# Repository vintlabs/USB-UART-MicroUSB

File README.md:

# USB-UART-MicroUSB
USB Serial UART with MicroUSB connector and RTS/DTR included in breakout (Hardware)

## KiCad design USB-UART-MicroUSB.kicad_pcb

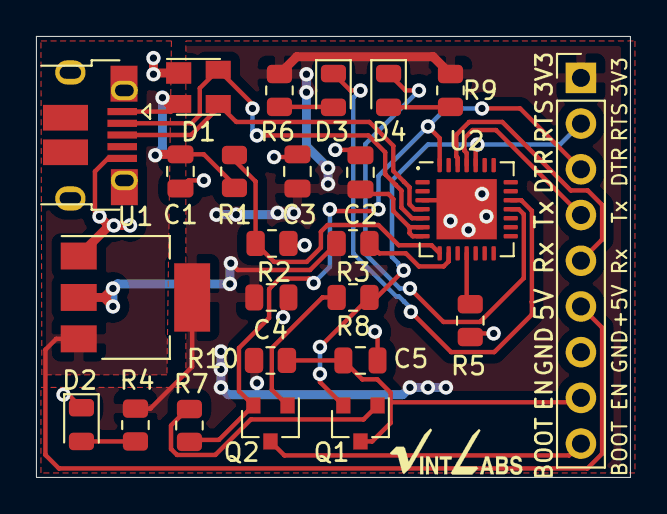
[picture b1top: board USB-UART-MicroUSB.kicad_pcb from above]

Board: 2 copper layers, 33.0 x 24.5 mm, 25 parts (0 on the bottom side), 21 nets.

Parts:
C1, C2, C4: 10u; C_0805_2012Metric
C3: 0.1u; C_0805_2012Metric
C5: 4.7u; C_0805_2012Metric
D1: SP0503BAHT; SOT-143
D2: LED; LED_0805_2012Metric
D3: LED YELLOW; LED_0805_2012Metric
D4: LED GREEN; LED_0805_2012Metric
J1: USB_B_Micro; USB_Micro-B_Amphenol_10118194-0001LF_Horizontal
J2: Conn_01x09_Male; PinHeader_1x09_P2.54mm_Vertical
Q1, Q2: MMBT2222A; SOT-23
R1: 22.1k; R_0805_2012Metric
R2: 47.5k; R_0805_2012Metric
R3: 1k; R_0805_2012Metric
R4, R6: 2.2k; R_0805_2012Metric
R5, R7, R8, R10: 10k; R_0805_2012Metric
R9: 4.7k; R_0805_2012Metric
U1: AP1117-33; SOT-223-3_TabPin2
U2: CP2102N-A01-GQFN28; QFN-28-1EP_5x5mm_P0.5mm_EP3.35x3.35mm

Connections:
DTR: J2.3, Q2.2, R7.2, U2.28
EN: C5.1, J2.8, Q1.3, R10.1
GND: C1.2, C2.2, C3.2, C4.2, C5.2, D1.1, D2.1, J1.5, J2.7, R2.2, R5.2, U1.1, U2.3, U2.29
IO0: J2.9, Q2.3
unnamed: D2.2, R4.2
unnamed: D3.2, R6.2
unnamed: D4.2, R9.2
unnamed: Q1.1, R7.1
unnamed: Q2.1, R8.1
unnamed: R1.2, R2.1, U2.8
unnamed: R3.2, U2.9
unnamed: R5.1, U2.11
RTS: J2.2, Q1.2, R8.2, U2.24
RXT: D3.1, U2.19
RxD: J2.4, U2.25
TXT: D4.1, U2.18
TxD: J2.5, U2.26
USB_DN: D1.4, J1.2, U2.5
USB_DP: D1.3, J1.3, U2.4
VBus: C1.1, D1.2, J1.1, J2.6, R1.1, U1.3
VDD: C2.1, C3.1, C4.1, J2.1, R3.1, R4.1, R6.1, R9.1, R10.2, U1.2, U2.6, U2.7

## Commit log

2020-12-19 Layout 90% complete
2020-12-22 Changed CP2102N to QFN28 (for availability reasons). Layout done.
